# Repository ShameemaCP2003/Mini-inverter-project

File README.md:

# Mini Inverter Project 

## Overview
This project is a compact mini inverter designed to convert DC power into AC output for low-power applications.

## Features
- Compact inverter circuit
- PCB-based design
- Power conversion system
- Electronic hardware integration

## Tools Used
- KiCad
- PCB Design
- Embedded Electronics

## Project Status
Ongoing Development

## Future Improvements
- Better efficiency
- Battery protection
- Compact enclosure
- Stable output waveform

## Author
Shameema C P

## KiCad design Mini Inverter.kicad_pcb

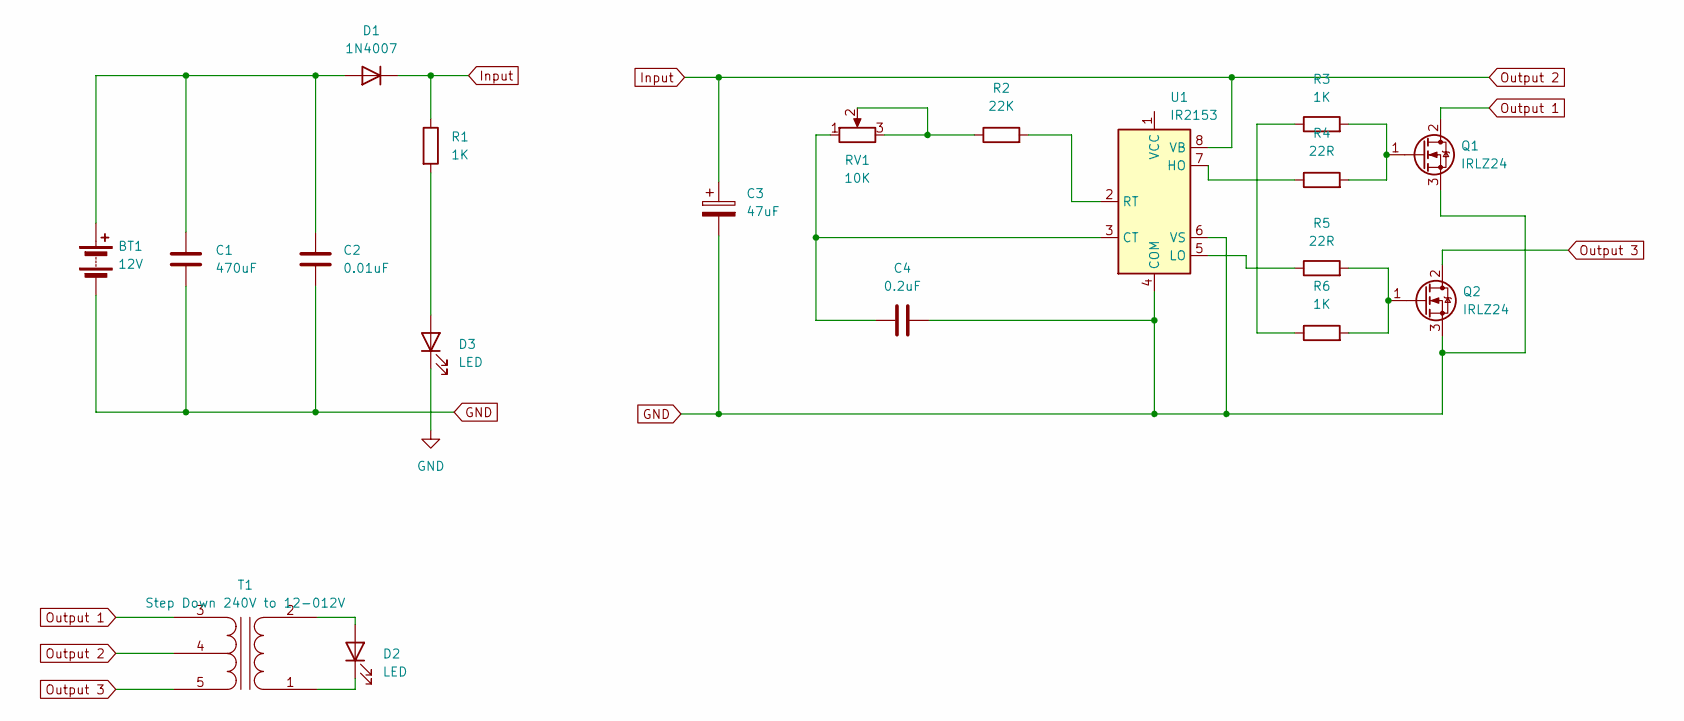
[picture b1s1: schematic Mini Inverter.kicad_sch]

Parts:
BT1: 12V; TerminalBlock_Xinya_XY308-2.54-2P_1x02_P2.54mm_Horizontal
C1: 470uF; CP_Radial_D6.3mm_P2.50mm
C2: 0.01uF; C_Disc_D3.0mm_W1.6mm_P2.50mm
C3: 47uF; CP_Radial_D5.0mm_P2.50mm
C4: 0.2uF; C_Disc_D3.0mm_W1.6mm_P2.50mm
D1: 1N4007; D_DO-41_SOD81_P10.16mm_Horizontal
D2: LED; TerminalBlock_Xinya_XY308-2.54-2P_1x02_P2.54mm_Horizontal
D3: LED; LED_D5.0mm
Q1, Q2: IRLZ24; TO-220-3_Vertical
R1, R3, R6: 1K; R_Axial_DIN0204_L3.6mm_D1.6mm_P5.08mm_Horizontal
R2: 22K; R_Axial_DIN0204_L3.6mm_D1.6mm_P5.08mm_Horizontal
R4, R5: 22R; R_Axial_DIN0204_L3.6mm_D1.6mm_P5.08mm_Horizontal
RV1: 10K; Potentiometer_ACP_CA6-H2,5_Horizontal
T1: Step Down 240V to 12-012V; TerminalBlock_Xinya_XY308-2.54-5P_1x05_P2.54mm_Horizontal
U1: IR2153; DIP-8_W7.62mm

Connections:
GND: BT1.2 (-), C1.2, C2.2, C3.2, C4.1, D3.1 (K), Q1.3 (S), Q2.3 (S), U1.4 (COM), U1.6 (VS)
Input: C3.1, D1.1 (K), R1.1, T1.4 (SC), U1.8 (VB)
unnamed: BT1.1 (+), C1.1, C2.1, D1.2 (A)
unnamed: D2.2 (A), T1.2 (AB)
unnamed: D2.1 (K), T1.1 (AA)
unnamed: D3.2 (A), R1.2
unnamed: Q1.1 (G), R3.2, R4.2
unnamed: Q2.1 (G), R5.2, R6.2
unnamed: R2.1, RV1.2, RV1.3
unnamed: R3.1, R6.1
unnamed: C4.2, RV1.1, U1.3 (CT)
unnamed: R4.1, U1.7 (HO)
unnamed: R5.1, U1.5 (LO)
unnamed: R2.2, U1.2 (RT)
Output 1: Q1.2 (D), T1.3 (SA)
Output 3: Q2.2 (D), T1.5 (SB)

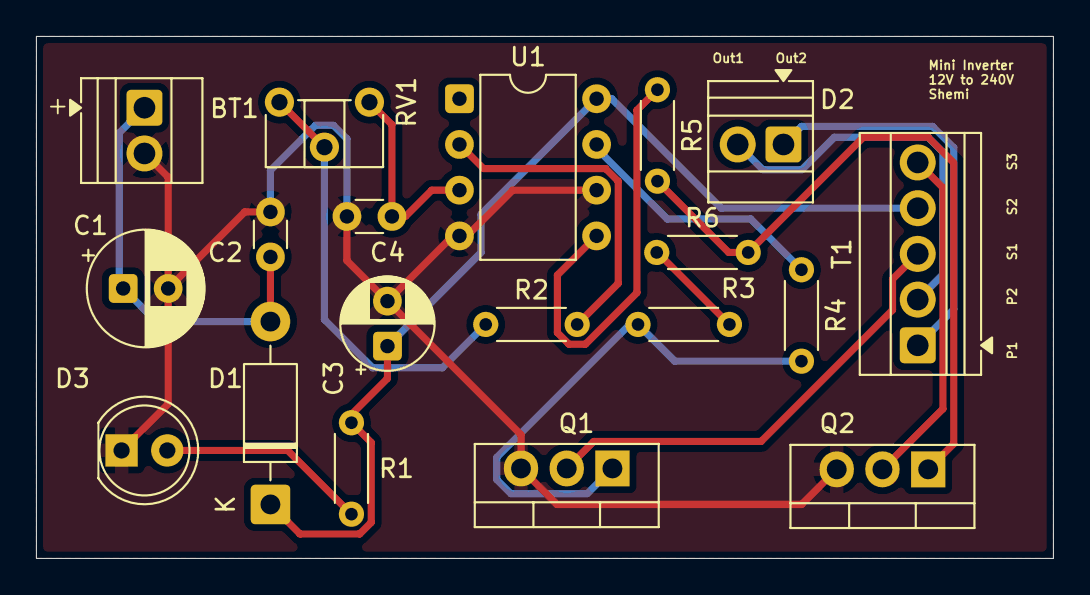
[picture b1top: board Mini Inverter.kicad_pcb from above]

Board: 2 copper layers, 56.5 x 29.0 mm, 19 parts (0 on the bottom side), 16 nets.
